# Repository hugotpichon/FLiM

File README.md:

*!!Pas encors fonctionel !!

PCB pour l'allimentation de moteur linéaire 
dans le cadre de la conception d'un flipper/pinball

logique 3V3/5V
entrée de puissance jusque à 24V (30?)
pas de filtre CEM

quelque obtion de réglage : diodes D1 et R0 change le dutycycle
C3 change la durée du déclanchement (24+ @ 100% durant x ms)

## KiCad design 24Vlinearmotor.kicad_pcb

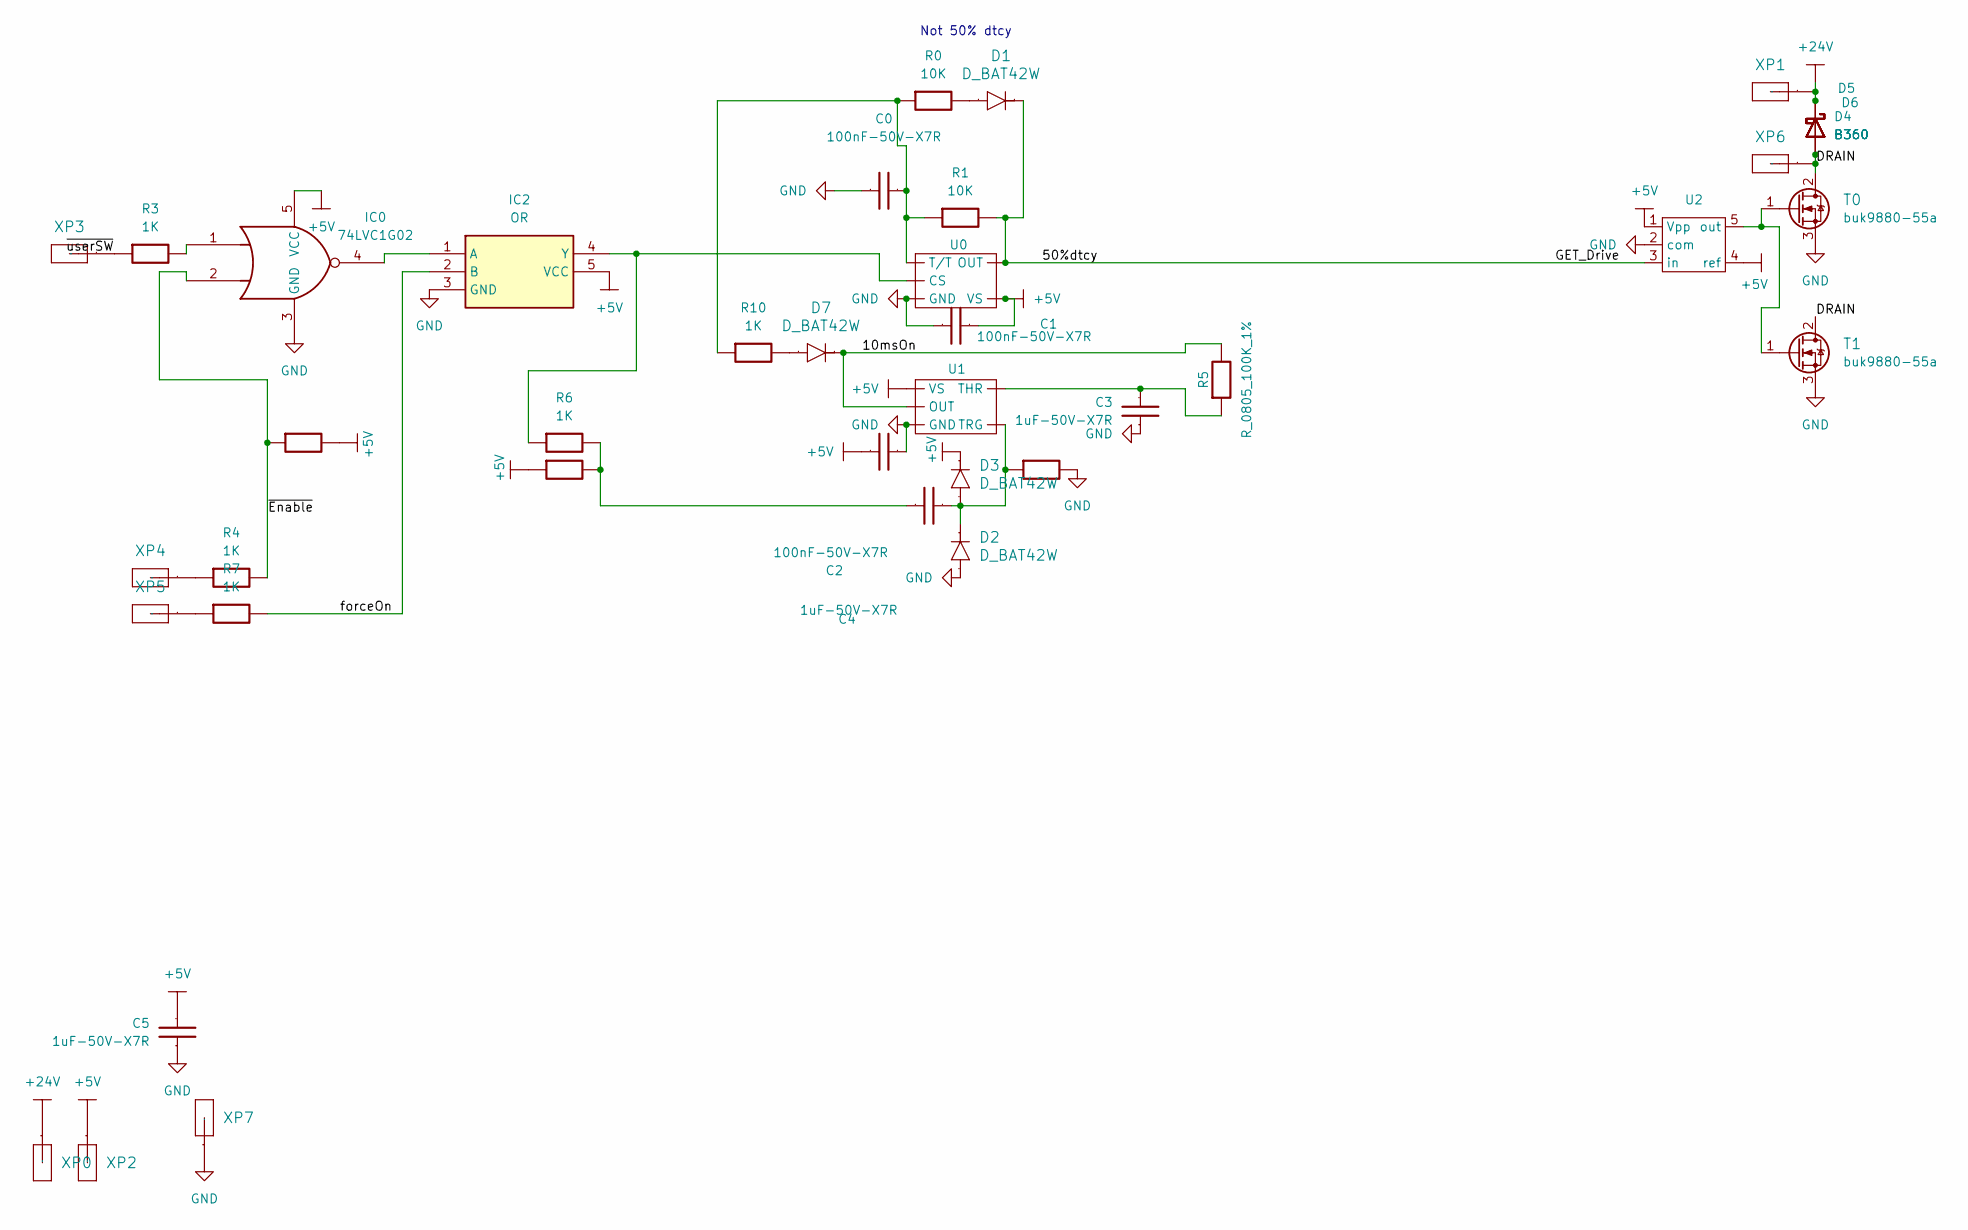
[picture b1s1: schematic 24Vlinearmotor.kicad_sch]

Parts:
C0, C1, C2: C_0805_100nF_50V_X7R_10%; C_0805_2012Metric_Pad1.15x1.40mm_HandSolder; Manufacturer Part Number CC0805KRX7R9BB104
C3, C4, C5: C_0805_1uF_50V_X7R_20%; C_0805_2012Metric; Manufacturer Part Number CL21B105MBFNNNE
D1, D2, D3, D7: D_BAT42W; D_SOD-123; Manufacturer Part Number BAT42W RHG
D4, D5, D6: B360; D_SMC
IC0: 74LVC1G02; SOT-23-5; Mouser Part Number 595-SN74LVC1G32DBVR
IC2: OR; SOT-23-5; Mouser Part Number 595-SN74LVC1G32DBVR
R0, R1: R_0805_10K_1%; R_0805_2012Metric_Pad1.15x1.40mm_HandSolder; Manufacturer Part Number RC0805FR-0710KL
R2, R5, R8, R9: R_0805_100K_1%; R_0805_2012Metric_Pad1.15x1.40mm_HandSolder; Manufacturer Part Number RC0805FR-07100KL
R3, R4, R6, R7: R_0805_1K_1%; R_0805_2012Metric_Pad1.15x1.40mm_HandSolder; Manufacturer Part Number RC0805FR-071KL
R10: R_0805_1K_1%; R_0805_2012Metric_Pad1.20x1.40mm_HandSolder; Manufacturer Part Number RC0805FR-071KL
T0, T1: buk9880-55a; SOT-223-3_TabPin2; Manufacturer Part Number IPD50N06S4L-12
U0: TSOT-23-5; Manufacturer Part Number MIC1553YM5-TR
U1: TSOT-23-5; Manufacturer Part Number MIC1551
U2: DGD0211EWT; TSOT-23-5; Manufacturer Part Number DGD0211EWT
XP0: +24; 2.8mm_Faston; Manufacturer Part Number 1267
XP1: +24_Mot; 2.8mm_Faston; Manufacturer Part Number 1267
XP2: +5; 2.8mm_Faston; Manufacturer Part Number 1267
XP3: !usr; 2.8mm_Faston; Manufacturer Part Number 1267
XP4: !En; 2.8mm_Faston; Manufacturer Part Number 1267
XP5: Frs; 2.8mm_Faston; Manufacturer Part Number 1267
XP6: Mot_2; 2.8mm_Faston; Manufacturer Part Number 1267
XP7: gnd; 2.8mm_Faston; Manufacturer Part Number 1267

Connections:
+5V: C1.2, C2.1, C5.2, D3.1, IC0.5 (VCC), IC2.5 (VCC), R2.2, R8.1, U0.4 (VS), U1.1 (VS), U2.1 (Vpp), U2.4 (ref), XP2.1
+24V: D4.1 (K), D5.1 (K), D6.1 (K), XP0.1, XP1.1
/10msOn: D7.1, R5.2, U1.3 (OUT)
/50%dtcy: D1.1, R1.2, U0.5 (OUT), U2.3 (in)
/DRAIN: D4.2 (A), D5.2 (A), D6.2 (A), T0.2 (D), T1.2 (D), XP6.1
/forceOn: IC2.2 (B), R7.2
/~Enable: IC0.2, R2.1, R4.2
/~userSW: R3.1, XP3.1
GND: C0.1, C1.1, C2.2, C3.1, C5.1, D2.2, IC0.3 (GND), IC2.3 (GND), R9.2, T0.3 (S), T1.3 (S), U0.2 (GND), U1.2 (GND), U2.2 (com), XP7.1
unnamed: C4.1, R6.2, R8.2
unnamed: D1.2, R0.2
unnamed: D7.2, R10.2
unnamed: IC0.1, R3.2
unnamed: IC0.4, IC2.1 (A)
unnamed: IC2.4 (Y), R6.1, U0.3 (CS)
unnamed: R4.1, XP4.1
unnamed: R7.1, XP5.1
unnamed: T0.1 (G), T1.1 (G), U2.5 (out)
unnamed: C0.2, R0.1, R1.1, R10.1, U0.1 (T/T)
unnamed: C3.2, R5.1, U1.5 (THR)
unnamed: C4.2, D2.1, D3.2, R9.1, U1.4 (TRG)

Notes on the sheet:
Not 50% dtcy

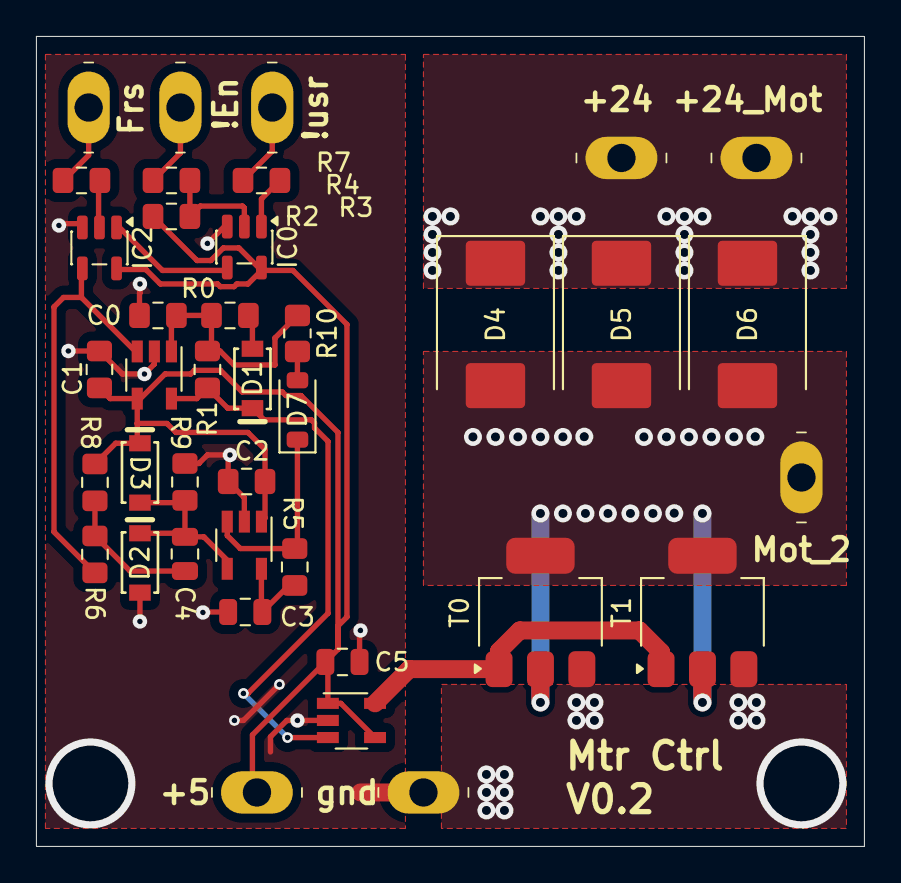
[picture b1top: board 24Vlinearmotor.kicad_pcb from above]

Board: 2 copper layers, 46.0 x 45.0 mm, 39 parts (0 on the bottom side), 21 nets.

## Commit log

2025-11-13 premier commit : creation git, mise à jour vers la version 0.2 : modification de la logique : logique positive pour "force" suppression d'une porte logique la monostable passe de 1 à 0 et fixe l'état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
    - testes effectué
    le système commute les transistors sous 5V sur résistance de 2.7koms
    l'astable fonctionne (mode dtcy 2/3)
2025-11-14 Update .gitignore
    exclude ipc files
